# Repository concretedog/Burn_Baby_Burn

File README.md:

# Burn_Baby_Burn
A small nichrome cutter for cut away systems

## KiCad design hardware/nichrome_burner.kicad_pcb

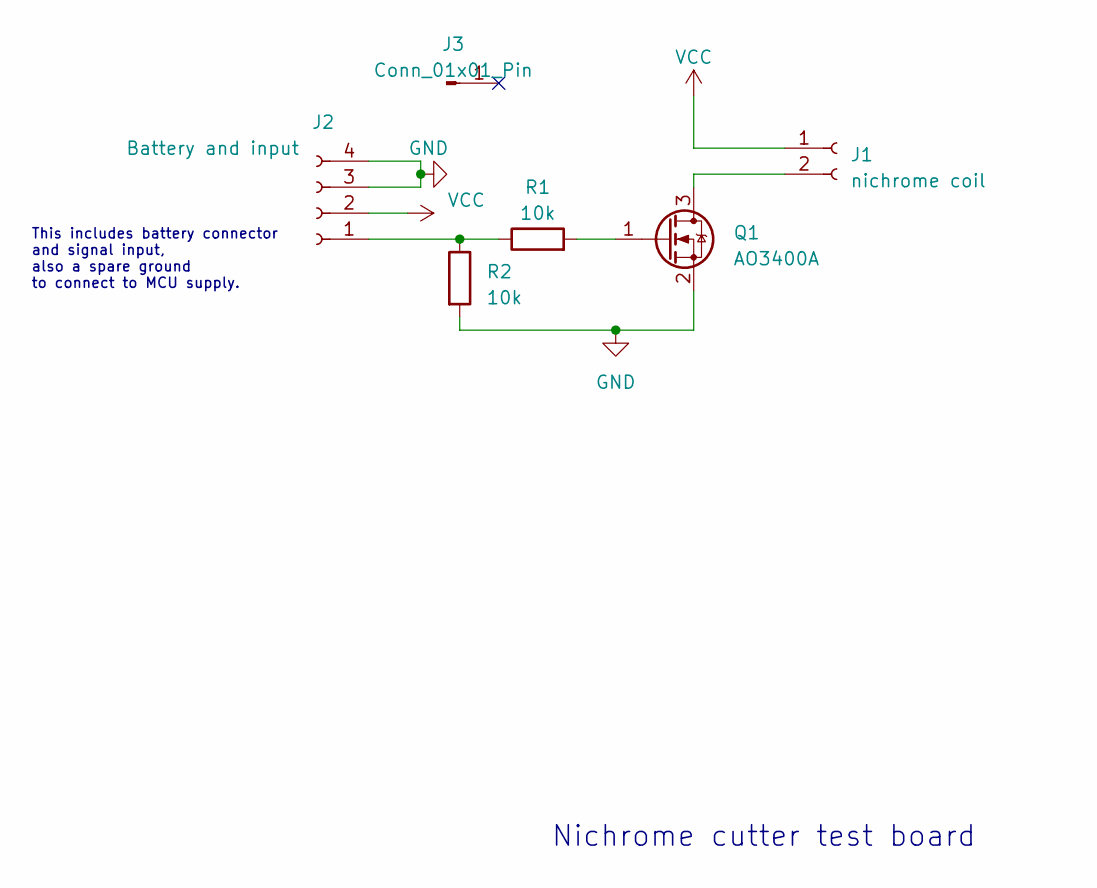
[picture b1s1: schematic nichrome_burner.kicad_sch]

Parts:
J1: nichrome coil; nichrome_coil_7mm
J2: Battery and input; PinHeader_1x04_P2.54mm_Vertical
J3: Conn_01x01_Pin; PinHeader_1x01_P2.54mm_Vertical
Q1: AO3400A; SOT-23; LCSC C20917
R1, R2: 10k; R_0805_2012Metric_Pad1.20x1.40mm_HandSolder; LCSC C17414

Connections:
GND: J2.3, J2.4, Q1.2 (S), R2.2
unnamed: J1.2, Q1.3 (D)
unnamed: J2.1, R1.1, R2.1
unnamed: Q1.1 (G), R1.2
VCC: J1.1, J2.2

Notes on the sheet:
This includes battery connector and signal input, also a spare ground to connect to MCU supply.
Nichrome cutter test board

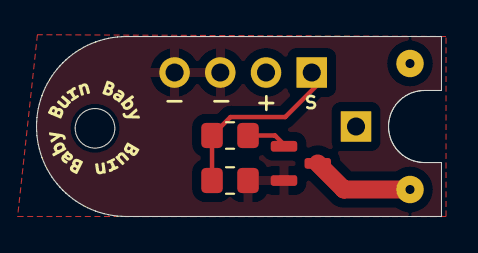
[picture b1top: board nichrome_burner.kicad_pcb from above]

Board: 2 copper layers, 22.5 x 10.0 mm, 6 parts (0 on the bottom side), 5 nets.

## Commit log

2023-05-29 Create test
2023-05-29 rename_tidy
2023-05-29 Update Burn_Baby_Burn_Pull_Pin_To_Fire.py
    removed elif, added freq initialise line
2023-05-29 Update Burn_Baby_Burn_Pull_Pin_To_Fire.py
    remove elif comment
2023-06-01 Update Burn_Baby_Burn_Pull_Pin_To_Fire.py
    comment tidying
